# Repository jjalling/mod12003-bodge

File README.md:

MOD12003 bodge board
====================

During testing, the linear driver on the MOD12003 was shown not to be robust
enough; it lost bias during an abusive "file" test (rapidly shorting/opening
the output by rubbing a wire over a file). This is an updated driver circuit
to be patched into Rev A of MOD12003.

This repository uses submodules. Download with `git clone --recursive`.

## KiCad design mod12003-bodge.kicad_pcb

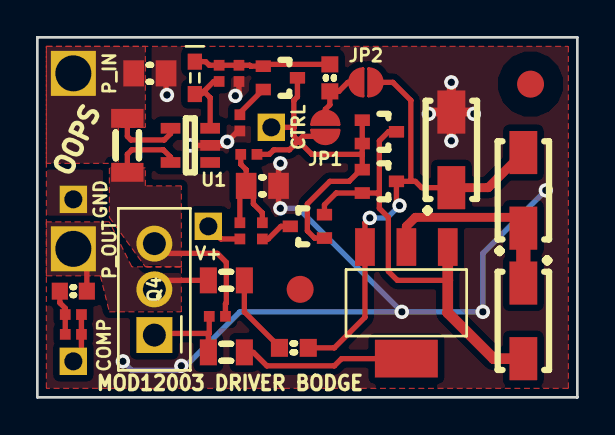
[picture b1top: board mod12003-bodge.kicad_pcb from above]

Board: 2 copper layers, 30.0 x 20.0 mm, 38 parts (0 on the bottom side), 20 nets.

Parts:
C1, C3: 100n; CAPC2012X70
C2, C5: 2n2; CAPC1608X55
D1, D2: BAT54AWT; SC-70
DS1: RED; LED-0603
DZ1, DZ2, DZ3: 24V; DIOM5226X203
E2: 120; INDC1608X95
FID1, FID2: FIDUCIAL-1.5mm
J1: V+; CONN-100MIL-F-1x1
J2: P_IN; CONN-100MIL-F-1x1
J3: GND; CONN-100MIL-F-1x1
J4: CTRL; CONN-100MIL-F-1x1
J5: COMP; CONN-100MIL-F-1x1
J6: P_OUT; CONN-100MIL-F-1x1
JP1: C2; JUMPER-SOLDER-SMD
JP2: C1; JUMPER-SOLDER-SMD
Q1, Q2: PMSS3904; SC-70
Q3: PZT3904; SOT-223
Q4: D45H11; TO-220
R1, R4: 47; RESC1005X40
R2: 30m; RESC3216X60
R3: 1k3; RESC1005X40
R5, R9, R11, R12: 20k; RESC1005X40
R6, R7: 220; RESC1005X40
R8, R10: 1R3; RESC2012X50
U1: ZXCT1110; SOT-23-5

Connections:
/P_IN: C1.1, J2.1, R2.2, U1.4
/P_OUT: C5.2, J6.1, Q4.2, R10.1
/P_SENSED: Q4.3, R2.1, R7.2, U1.5
GND: C1.2, C3.2, DZ3.2, J3.1, R3.2, R4.2, U1.2
unnamed: C2.1, JP1.1, JP2.1
unnamed: C2.2, DS1.1, Q1.1, R3.1, R11.1
unnamed: C3.1, R1.1, R5.1, R6.1
unnamed: C5.1, R9.2, R12.2
unnamed: D1.1, D1.2, D2.1, J4.1, JP1.2, Q1.3, Q2.1, R5.2
unnamed: D1.3, D2.2, DZ1.2, Q2.2, Q3.1
unnamed: D2.3, DZ2.2, DZ3.1, E2.2, JP2.2, Q3.3
unnamed: DS1.2, R11.2, U1.3
unnamed: DZ1.1, DZ2.1, Q3.2
unnamed: E2.1, R10.2
unnamed: J1.1, R1.2
unnamed: J5.1, R9.1, R12.1
unnamed: Q1.2, R4.1
unnamed: Q2.3, R6.2
unnamed: Q3.4, R8.2
unnamed: Q4.1, R7.1, R8.1

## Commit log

2016-02-25 Add submodules
2016-02-25 Add KiCad files
2016-02-25 Production version
2016-02-25 Add readme
